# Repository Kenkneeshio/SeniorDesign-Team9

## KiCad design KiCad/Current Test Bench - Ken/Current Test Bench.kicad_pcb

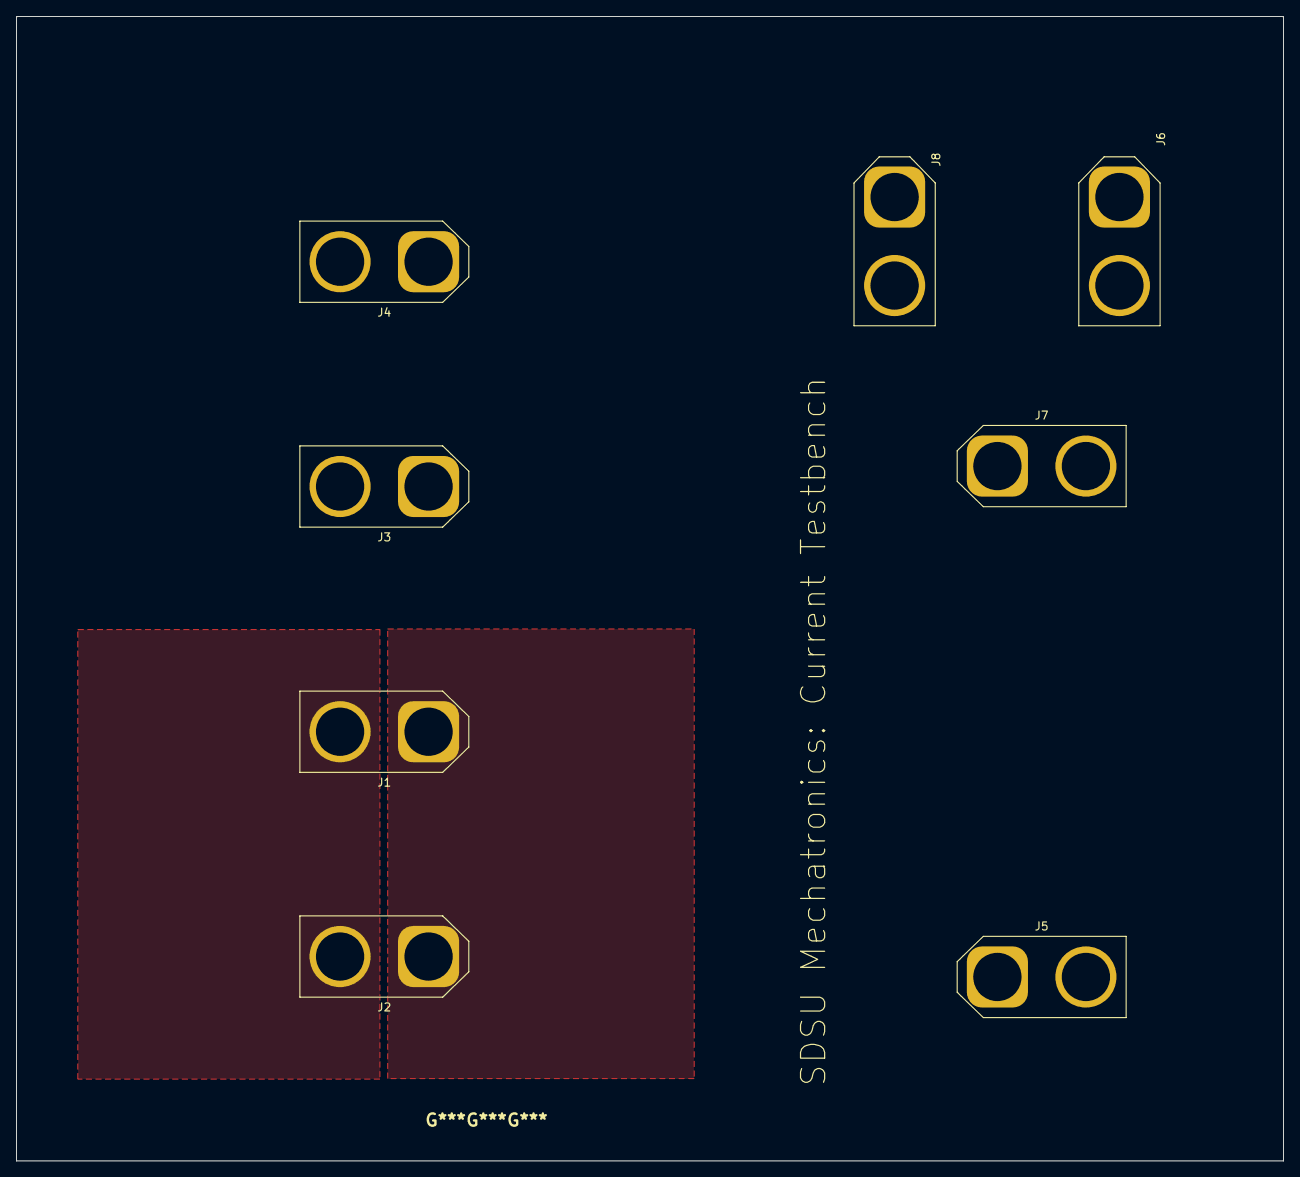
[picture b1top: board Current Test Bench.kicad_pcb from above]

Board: 2 copper layers, 157.5 x 142.2 mm, 8 parts (0 on the bottom side), 8 nets, no tracks yet.

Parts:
J1, J3, J5, J6: XT90 IN; AMASS_XT90-M_1x02_P11.00mm_Vertical
J2, J4, J7, J8: XT90 Out; AMASS_XT90-M_1x02_P11.00mm_Vertical

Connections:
/GND: J1.1, J2.1
/GND2: J5.1, J7.1
/GND3: J3.1, J4.1
/GND4: J6.1, J8.1
/VIN: J1.2, J2.2
/VIN2: J5.2, J7.2
/VIN3: J3.2, J4.2
/VIN4: J6.2, J8.2

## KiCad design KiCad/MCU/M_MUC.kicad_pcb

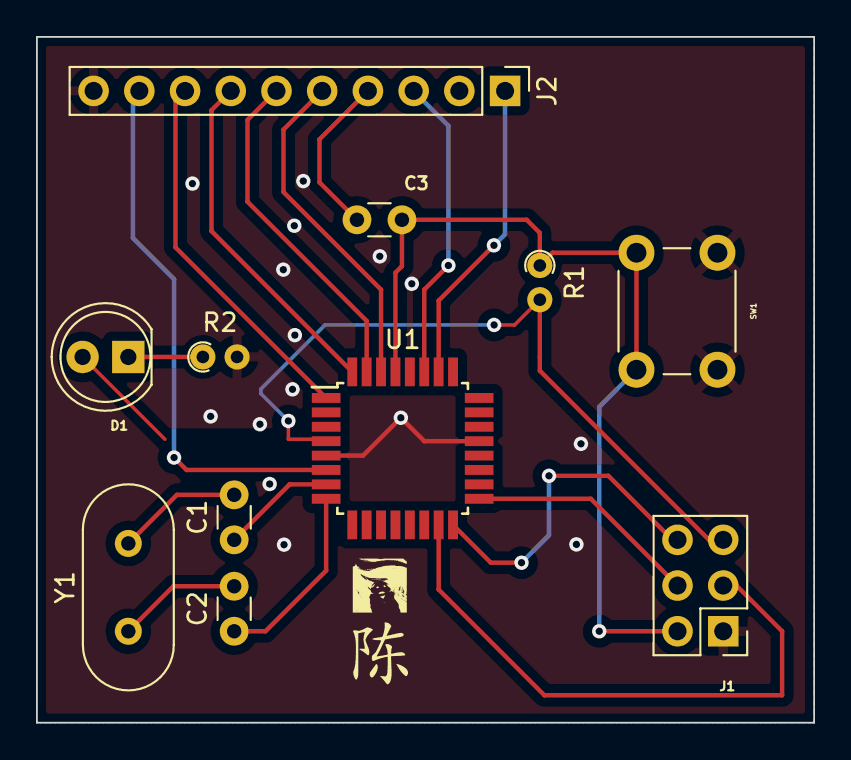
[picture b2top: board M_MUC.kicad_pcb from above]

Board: 2 copper layers, 43.2 x 38.1 mm, 11 parts (0 on the bottom side), 19 nets.

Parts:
C1, C2: 22pF; C_Disc_D3.0mm_W1.6mm_P2.50mm
C3: 100nF; C_Disc_D3.0mm_W1.6mm_P2.50mm
D1: LED; LED_D5.0mm
J1: 6pin; PinHeader_2x03_P2.54mm_Vertical
J2: Conn_01x10; PinHeader_1x10_P2.54mm_Vertical
R1: 10K; R_Axial_DIN0204_L3.6mm_D1.6mm_P1.90mm_Vertical
R2: 1k; R_Axial_DIN0204_L3.6mm_D1.6mm_P1.90mm_Vertical
SW1: SW_Push_Open; SW_PUSH_6mm
U1: ATmega328PB-A; TQFP-32_7x7mm_P0.8mm
Y1: Crystal; Crystal_HC49-4H_Vertical

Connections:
5V: J1.5, R1.2, U1.4 (VCC)
/rst: C3.2, J2.4
/rx: J2.5, U1.30 (PD0)
/tx: J2.6, U1.31 (PD1)
GND: J1.1, J2.10, R2.2, SW1.1 (A), U1.5 (GND), U1.21 (GND)
MISO: J1.6, U1.16 (PB4)
MOSI: J1.3, U1.15 (PB3)
unnamed: C1.2, Y1.2
unnamed: C2.2, Y1.1
unnamed: D1.1 (K), R2.1
unnamed: J2.1, U1.26 (PC3)
unnamed: J2.3, U1.27 (PC4)
unnamed: J2.7, U1.32 (PD2)
unnamed: J2.8, U1.1 (PD3)
unnamed: J2.9, U1.6 (PE1)
unnamed: C1.1, U1.7 (XTAL1/PB6)
unnamed: C2.1, U1.8 (XTAL2/PB7)
RST: C3.1, J1.2, R1.1, SW1.2 (B), U1.29 (~RESET/PC6)
SCK: J1.4, U1.17 (PB5)

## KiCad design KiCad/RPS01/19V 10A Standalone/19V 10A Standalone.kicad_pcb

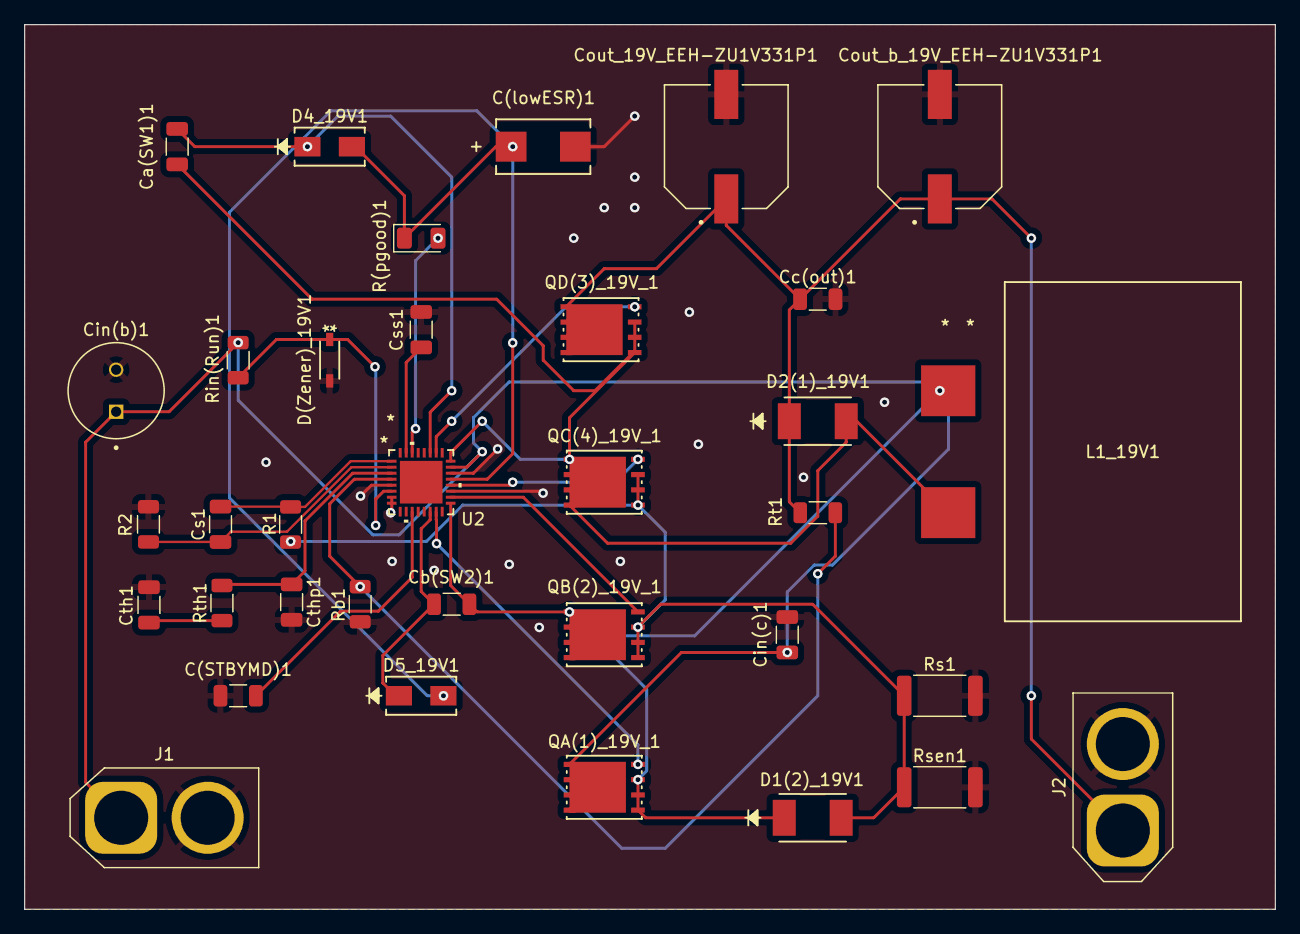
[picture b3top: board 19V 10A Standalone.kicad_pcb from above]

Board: 2 copper layers, 104.1 x 73.7 mm, 35 parts (0 on the bottom side), 22 nets.

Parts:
C(STBYMD)1: 0.001u; C_1206_3216Metric
C(lowESR)1: 4.7u; CAPMP7.6X4.3_3.1N_KEM
Ca(SW1)1: 0.22u; C_1206_3216Metric
Cb(SW2)1: 0.22u; C_1206_3216Metric
Cc(out)1: 47u; C_1206_3216Metric
Cin(b)1: 270u; LargeCAPSCAPPRD350W60D800H1200
Cin(c)1: 10u; C_1206_3216Metric
Cout_19V_EEH-ZU1V331P1: 330u; CAP_EEHZU1V331P
Cout_b_19V_EEH-ZU1V331P1: 330u; CAP_EEHZU1V331P
Cs1: 100p; C_1206_3216Metric
Css1: 0.001u; C_1206_3216Metric
Cth1: 10000p; C_1206_3216Metric
Cthp1: 47p; C_1206_3216Metric
D1(2)_19V1, D2(1)_19V1: SD2114S040S8R0; SD2114_AVX
D4_19V1, D5_19V1: D_Schottky_B340AE-13; CR_SMA_320-340AE_DIO
D(Zener)_19V1: D_Zener_BZT52C4V7-13-F; SOD123_DIO
J1: Conn_01x02_Socket; AMASS_XT60-M_1x02_P7.20mm_Vertical
J2: Conn_01x02_Socket; AMASS_XT60-F_1x02_P7.20mm_Vertical
L1_19V1: 6.8u Wurth 74436410680; IND_410680_WRE
QA(1)_19V_1: BSC009NE2LS5IATMA1; PG-TDSON-8_INF_modified_ken
QB(2)_19V_1: BSC009NE2LS5IATMA1; PG-TDSON-8_INF_modified_ken
QC(4)_19V_1: BSC009NE2LS5IATMA1; PG-TDSON-8_INF_modified_ken
QD(3)_19V_1: BSC009NE2LS5IATMA1; PG-TDSON-8_INF_modified_ken
R1, R2: 100; R_1206_3216Metric
R(pgood)1: 100k; LED_1206_3216Metric
Rb1: 4.3K; R_1206_3216Metric
Rin(Run)1: 51K; R_1206_3216Metric
Rs1: 6m; R_2512_6332Metric
Rsen1: 6m; R_2512_6332Metric
Rt1: 100K; R_1206_3216Metric
Rth1: 124K; R_1206_3216Metric
U2: LTC3780EUH-TRPBF; QFN-32_UH_LIT

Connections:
/BG1: QC(4)_19V_1.4, U2.20 (BG1)
/BG2: QB(2)_19V_1.4, U2.18 (BG2)
/BOOST1: Ca(SW1)1.1, D4_19V1.1 (K), U2.27 (BOOST1)
/BOOST2: Cb(SW2)1.2, D5_19V1.1 (K), U2.14 (BOOST2)
/INTVCC: C(lowESR)1.1, D4_19V1.2 (A), D5_19V1.2 (A), R(pgood)1.1, U2.21 (INTVCC)
/ITH: Cthp1.1, Rth1.2, U2.3 (ITH)
/PGOOD: R(pgood)1.2, U2.30 (PGOOD)
/Rsense: D1(2)_19V1.2, QB(2)_19V_1.1, QB(2)_19V_1.2, QB(2)_19V_1.3, QC(4)_19V_1.1, QC(4)_19V_1.2, QC(4)_19V_1.3, R1.1, Rs1.1, Rsen1.1
/Run: D(Zener)_19V1.1 (K), Rin(Run)1.2, U2.6 (RUN)
/SENSE+: Cs1.2, R1.2, U2.1 (SENSE+)
/SENSE-: Cs1.1, R2.1, U2.2 (SENSE-)
/SS: Css1.2, U2.31 (SS)
/STBYMD: C(STBYMD)1.1, U2.11 (STBYMD)
/SW1: Ca(SW1)1.2, D2(1)_19V1.2, L1_19V1.2, QC(4)_19V_1.5, QC(4)_19V_1.6, QC(4)_19V_1.7, QC(4)_19V_1.8, QD(3)_19V_1.1, QD(3)_19V_1.2, QD(3)_19V_1.3, U2.24 (SW1)
/SW2: Cb(SW2)1.1, D1(2)_19V1.1, L1_19V1.1, QA(1)_19V_1.1, QA(1)_19V_1.2, QA(1)_19V_1.3, QB(2)_19V_1.5, QB(2)_19V_1.6, QB(2)_19V_1.7, QB(2)_19V_1.8, U2.17 (SW2)
/TG1: QD(3)_19V_1.4, U2.26 (TG1)
/TG2: QA(1)_19V_1.4, U2.15 (TG2)
/VOSENSE: Rb1.1, Rt1.2, U2.4 (VOSENSE)
/Vin: Cin(b)1.1, Cin(c)1.1, J1.1, QA(1)_19V_1.5, QA(1)_19V_1.6, QA(1)_19V_1.7, QA(1)_19V_1.8, Rin(Run)1.1, U2.23 (VIN)
/Vout: Cc(out)1.1, Cout_19V_EEH-ZU1V331P1.1, Cout_b_19V_EEH-ZU1V331P1.1, D2(1)_19V1.1, J2.1, QD(3)_19V_1.5, QD(3)_19V_1.6, QD(3)_19V_1.7, QD(3)_19V_1.8, Rt1.1
GND: C(STBYMD)1.2, C(lowESR)1.2, Cc(out)1.2, Cin(b)1.2, Cin(c)1.2, Cout_19V_EEH-ZU1V331P1.2, Cout_b_19V_EEH-ZU1V331P1.2, Css1.1, Cth1.2, Cthp1.2, D(Zener)_19V1.2 (A), J1.2, J2.2, R2.2, Rb1.2, Rs1.2, Rsen1.2, U2.5 (SGND), U2.7 (FCB), U2.8 (PLLFLTR), U2.19 (PGND), U2.22 (EXTVCC)
unnamed: Cth1.1, Rth1.1
